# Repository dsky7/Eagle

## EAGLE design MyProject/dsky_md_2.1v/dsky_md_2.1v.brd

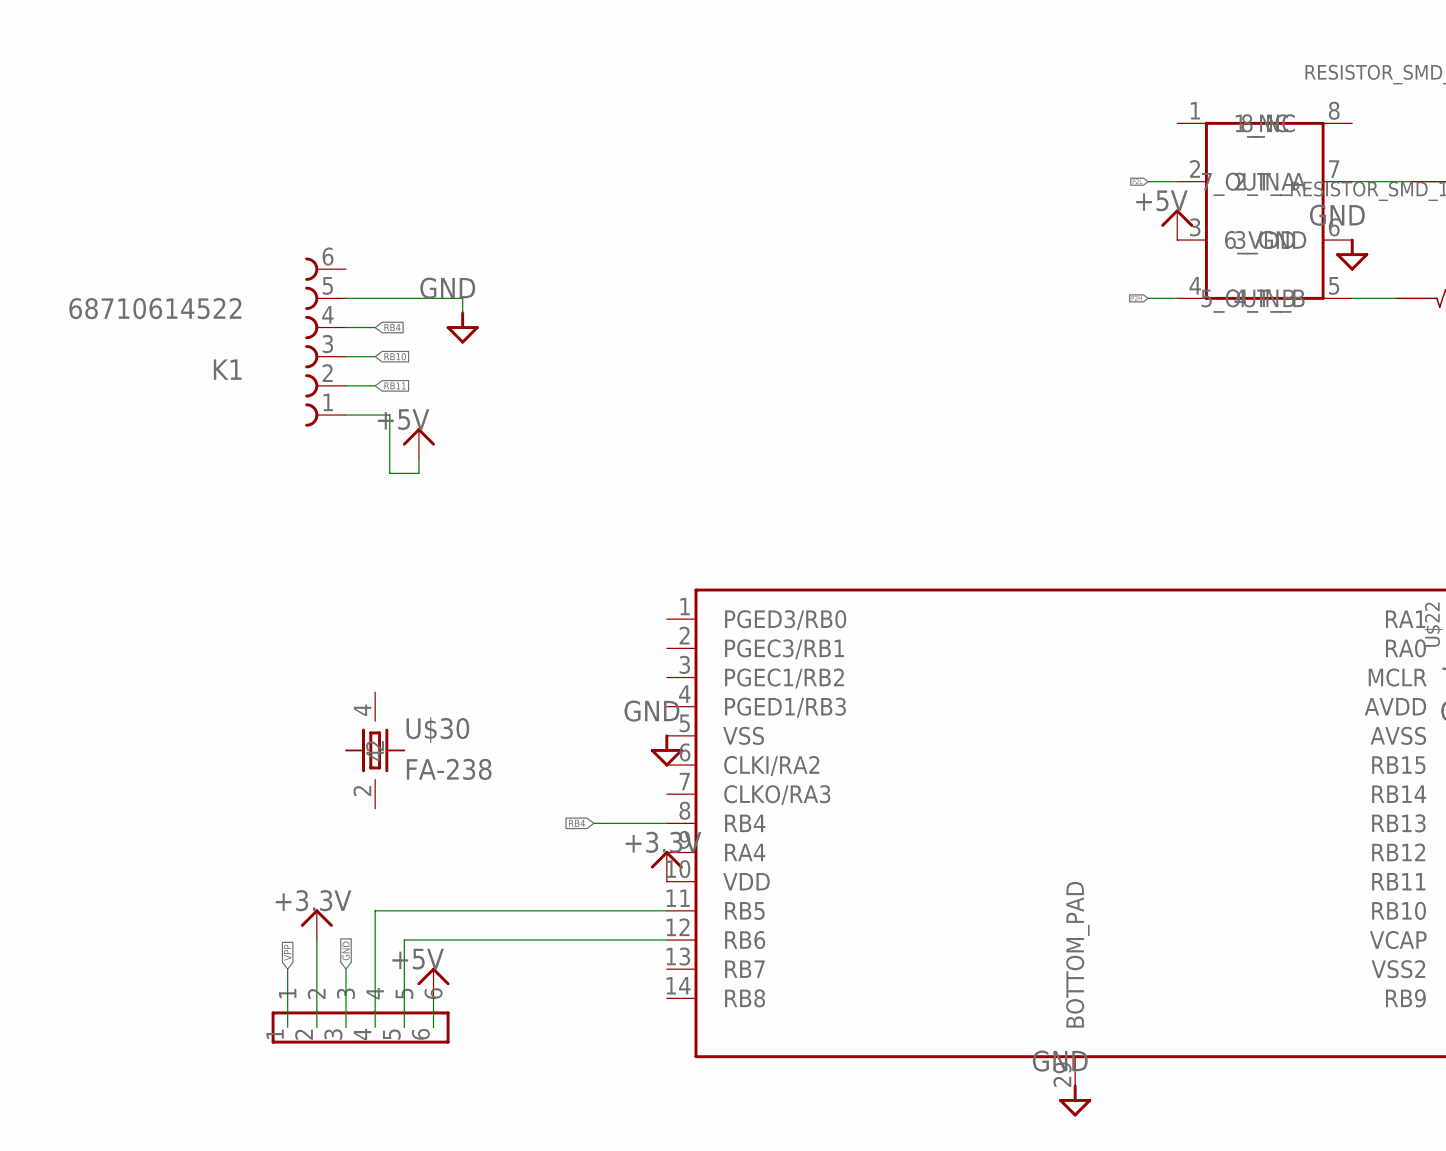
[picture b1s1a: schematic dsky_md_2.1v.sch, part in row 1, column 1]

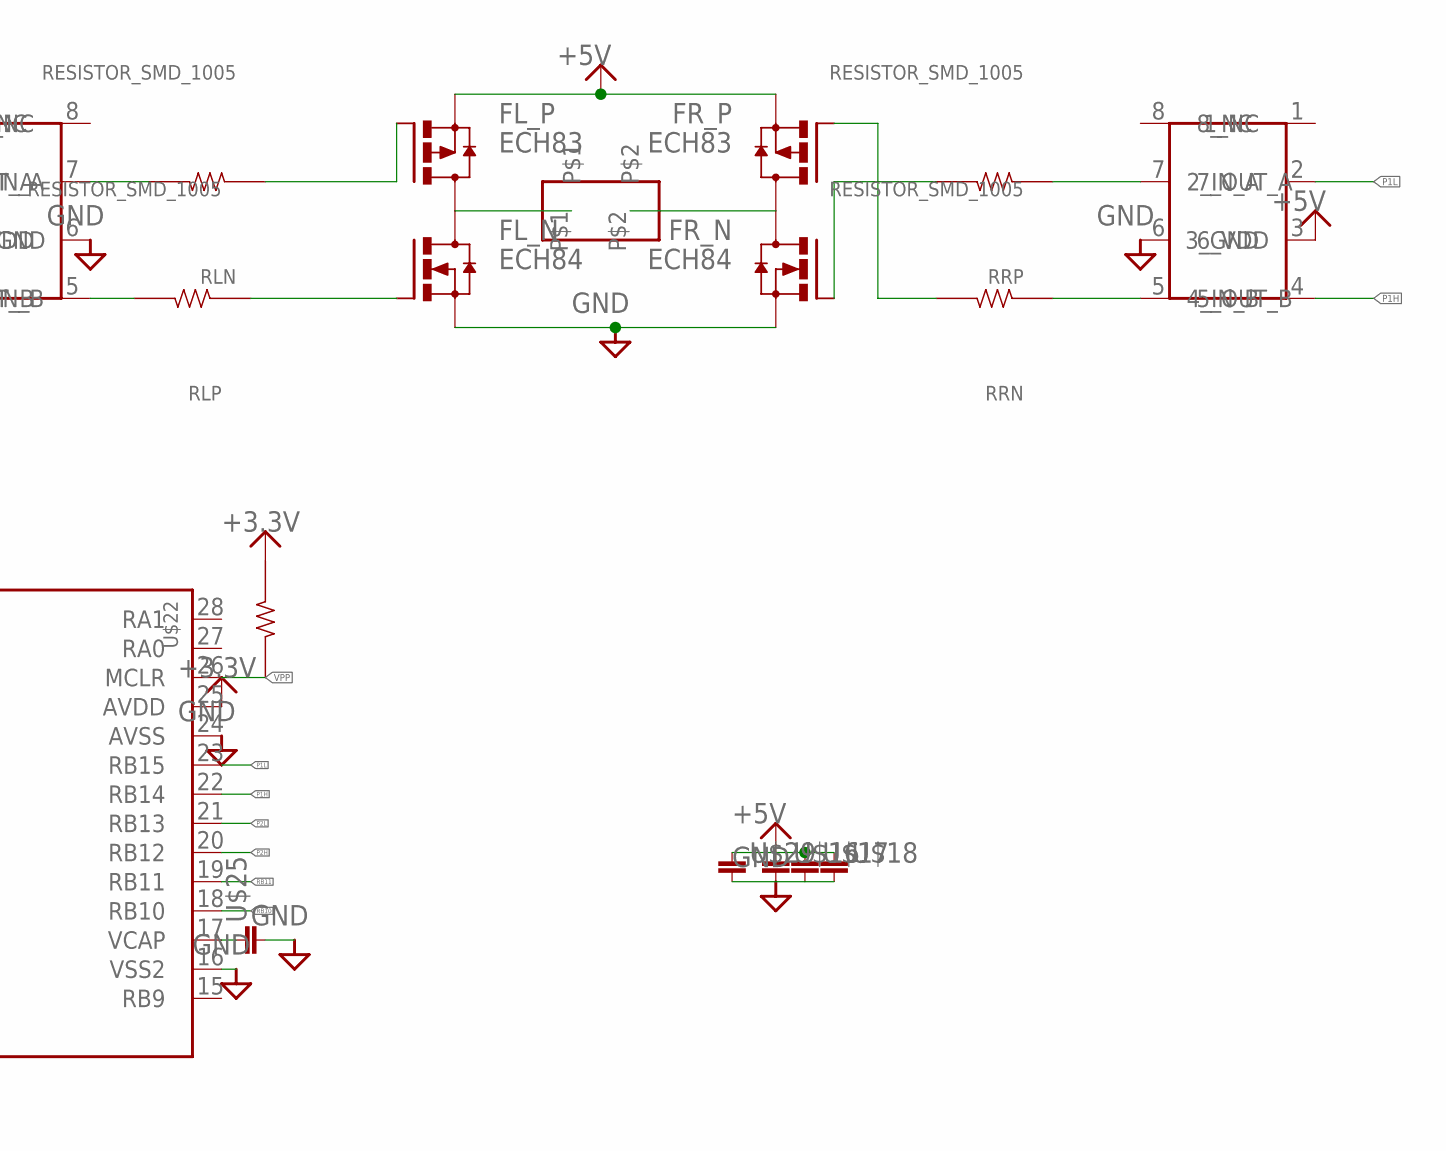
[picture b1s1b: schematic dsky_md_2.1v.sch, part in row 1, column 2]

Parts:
FL_N: ECH84; ECH8
FL_P: ECH83; ECH8
FR_N: ECH84; ECH8
FR_P: ECH83; ECH8
IC_L: TC1427COA; SOIC8
IC_R: TC1427COA; SOIC8
K1: 68710614522
RLN: RESISTOR_SMD_1005; 1005
RLP: RESISTOR_SMD_1005; 1005
RRN: RESISTOR_SMD_1005; 1005
RRP: RESISTOR_SMD_1005; 1005
U$3: PIN_HEADER_2; PIN_HEADER_2S
U$5: DSPIC33EP32MC202; QFN-S28_6X6MC
U$6: PIN_HEADER_HALF_6
U$16, U$17, U$18, U$25: 1608
U$22: RESISTOR__SMD; 1608
U$29: 2012
U$30: FA-238

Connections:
+3.3V: U$5.10 (VDD), U$5.25 (AVDD), U$6.2, U$22.2
+5V: FL_P.1 (S), FL_P.2 (S), FL_P.3 (S), FR_P.1 (S), FR_P.2 (S), FR_P.3 (S), IC_L.3 (3_GND), IC_R.3 (3_GND), K1.1, U$6.6, U$16.P$1 (1), U$17.P$1 (1), U$18.P$1 (1), U$29.1
GND: FL_N.1 (S), FL_N.2 (S), FL_N.3 (S), FR_N.1 (S), FR_N.2 (S), FR_N.3 (S), IC_L.6 (6_VDD), IC_R.6 (6_VDD), K1.5, U$5.5 (VSS), U$5.16 (VSS2), U$5.24 (AVSS), U$5.29 (BOTTOM_PAD), U$6.3, U$16.P$2 (2), U$17.P$2 (2), U$18.P$2 (2), U$25.P$2 (2), U$29.2
M_L: FL_N.5 (D), FL_N.6 (D), FL_N.7 (D), FL_N.8 (D), FL_P.5 (D), FL_P.6 (D), FL_P.7 (D), FL_P.8 (D), U$3.P$1
M_R: FR_N.5 (D), FR_N.6 (D), FR_N.7 (D), FR_N.8 (D), FR_P.5 (D), FR_P.6 (D), FR_P.7 (D), FR_P.8 (D), U$3.P$2
unnamed: FL_P.4 (G), RLN.1
unnamed: FL_N.4 (G), RLP.1
unnamed: IC_L.7 (7_OUT_A), RLN.2
unnamed: FR_P.4 (G), RRN.2
unnamed: IC_L.5 (5_OUT_B), RLP.2
unnamed: IC_R.7 (7_OUT_A), RRP.1
unnamed: U$5.17 (VCAP), U$25.P$1 (1)
unnamed: IC_R.5 (5_OUT_B), RRN.1
unnamed: U$5.11 (RB5), U$6.4
unnamed: U$5.12 (RB6), U$6.5
unnamed: FR_N.4 (G), RRP.2
P1H: IC_R.4 (4_IN_B), U$5.22 (RB14)
P1L: IC_R.2 (2_IN_A), U$5.23 (RB15)
P2H: IC_L.4 (4_IN_B), U$5.20 (RB12)
P2L: IC_L.2 (2_IN_A), U$5.21 (RB13)
RB4: K1.4, U$5.8 (RB4)
RB10: K1.3, U$5.18 (RB10)
RB11: K1.2, U$5.19 (RB11)
VPP: U$5.26 (MCLR), U$6.1, U$22.1

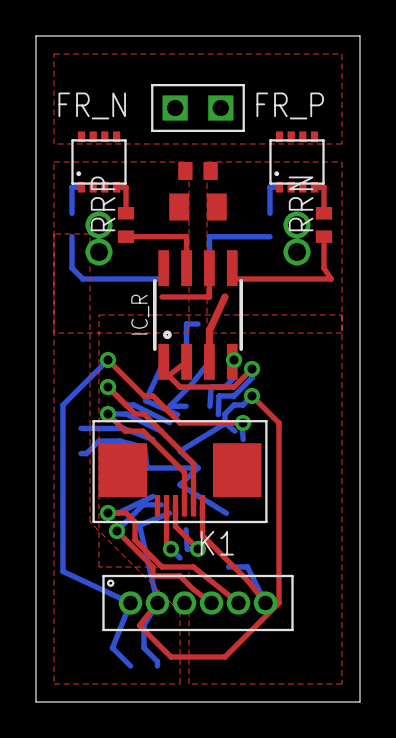
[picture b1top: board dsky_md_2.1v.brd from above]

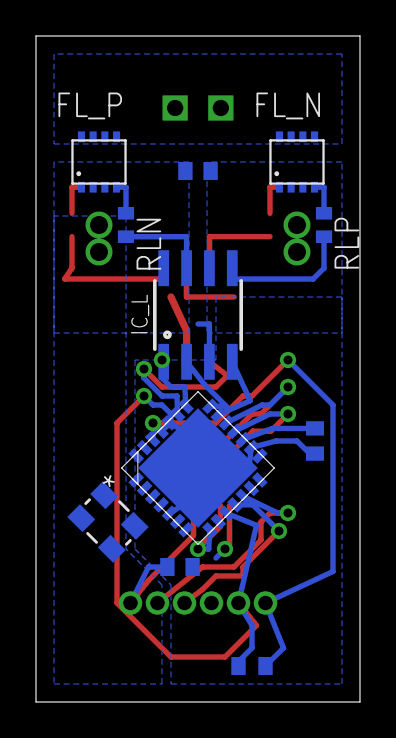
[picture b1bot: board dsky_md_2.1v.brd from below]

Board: 2 copper layers, 18.0 x 37.0 mm, 21 parts (11 on the bottom side), 24 nets.

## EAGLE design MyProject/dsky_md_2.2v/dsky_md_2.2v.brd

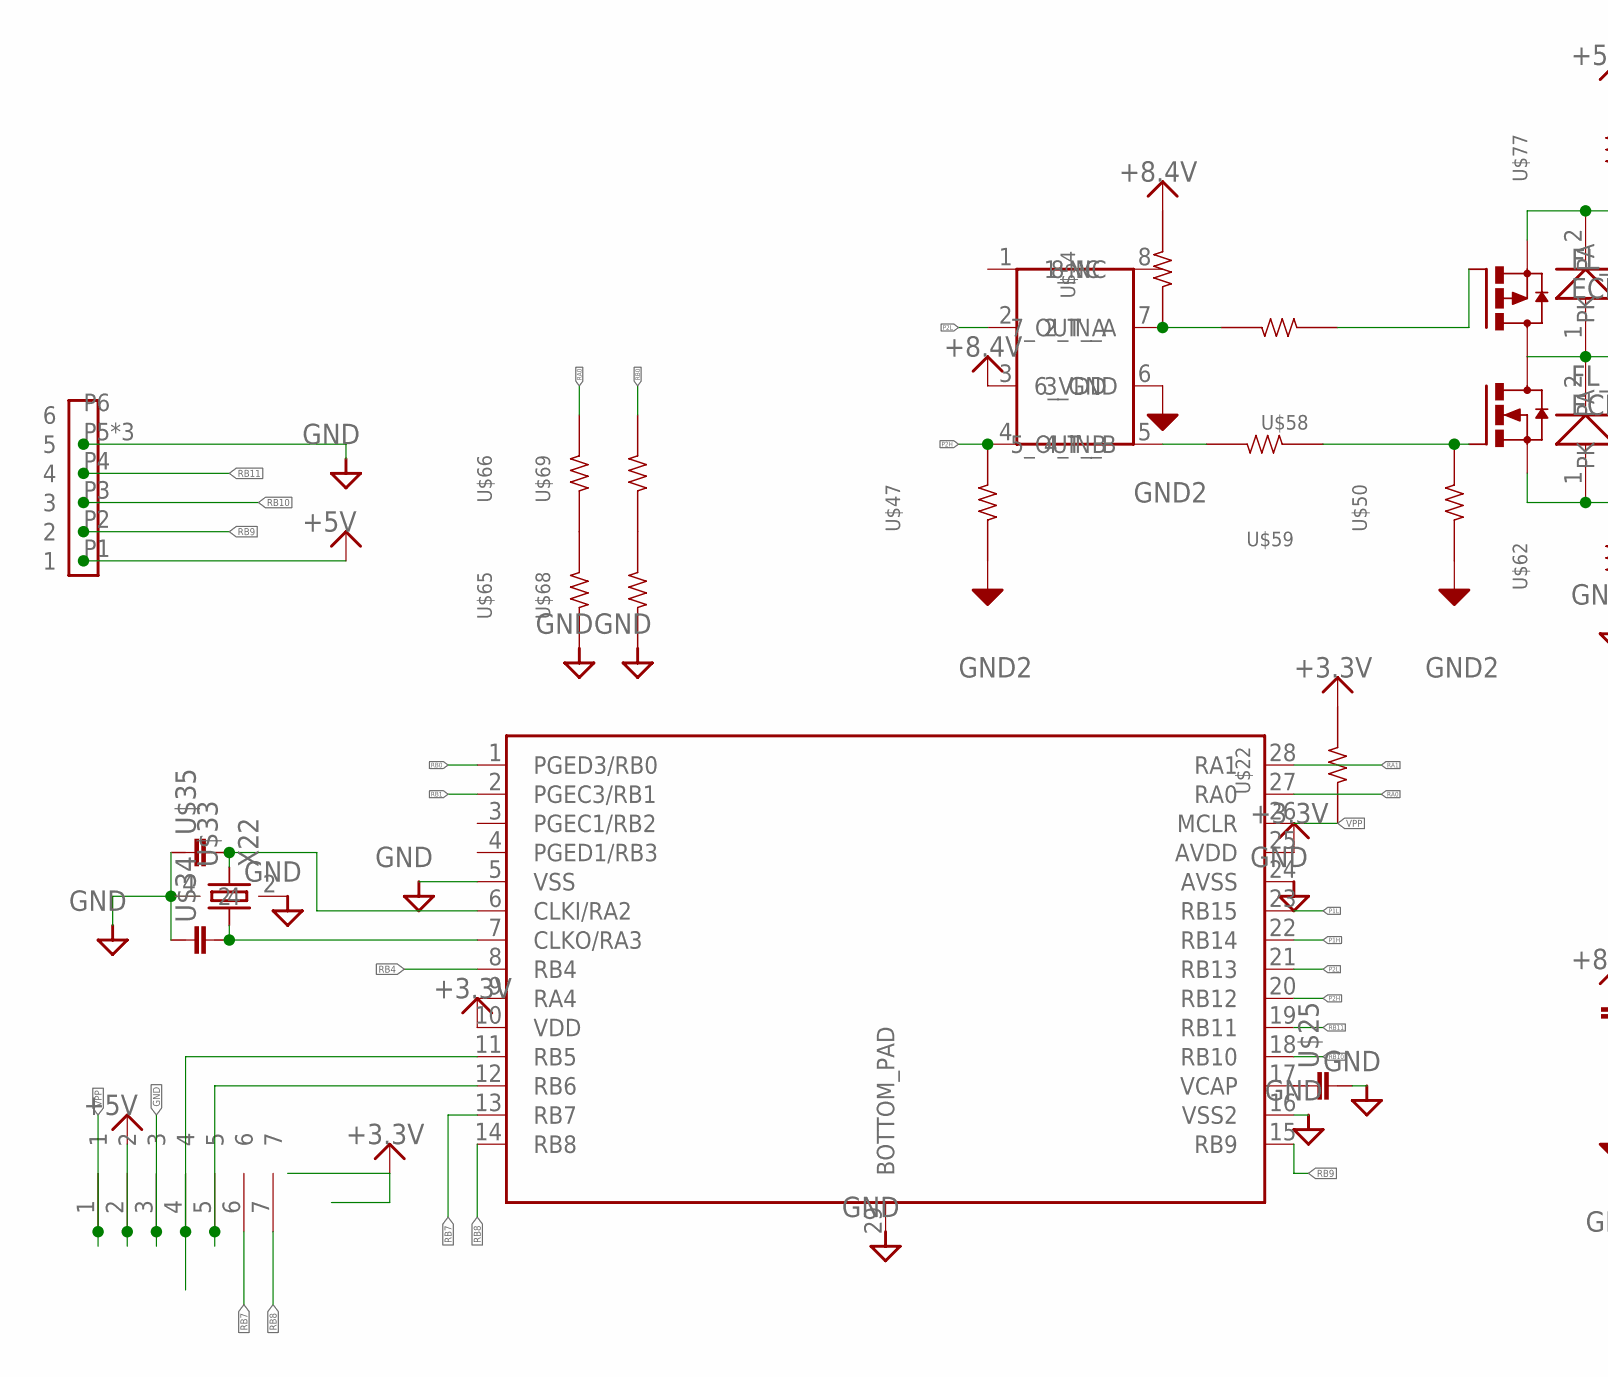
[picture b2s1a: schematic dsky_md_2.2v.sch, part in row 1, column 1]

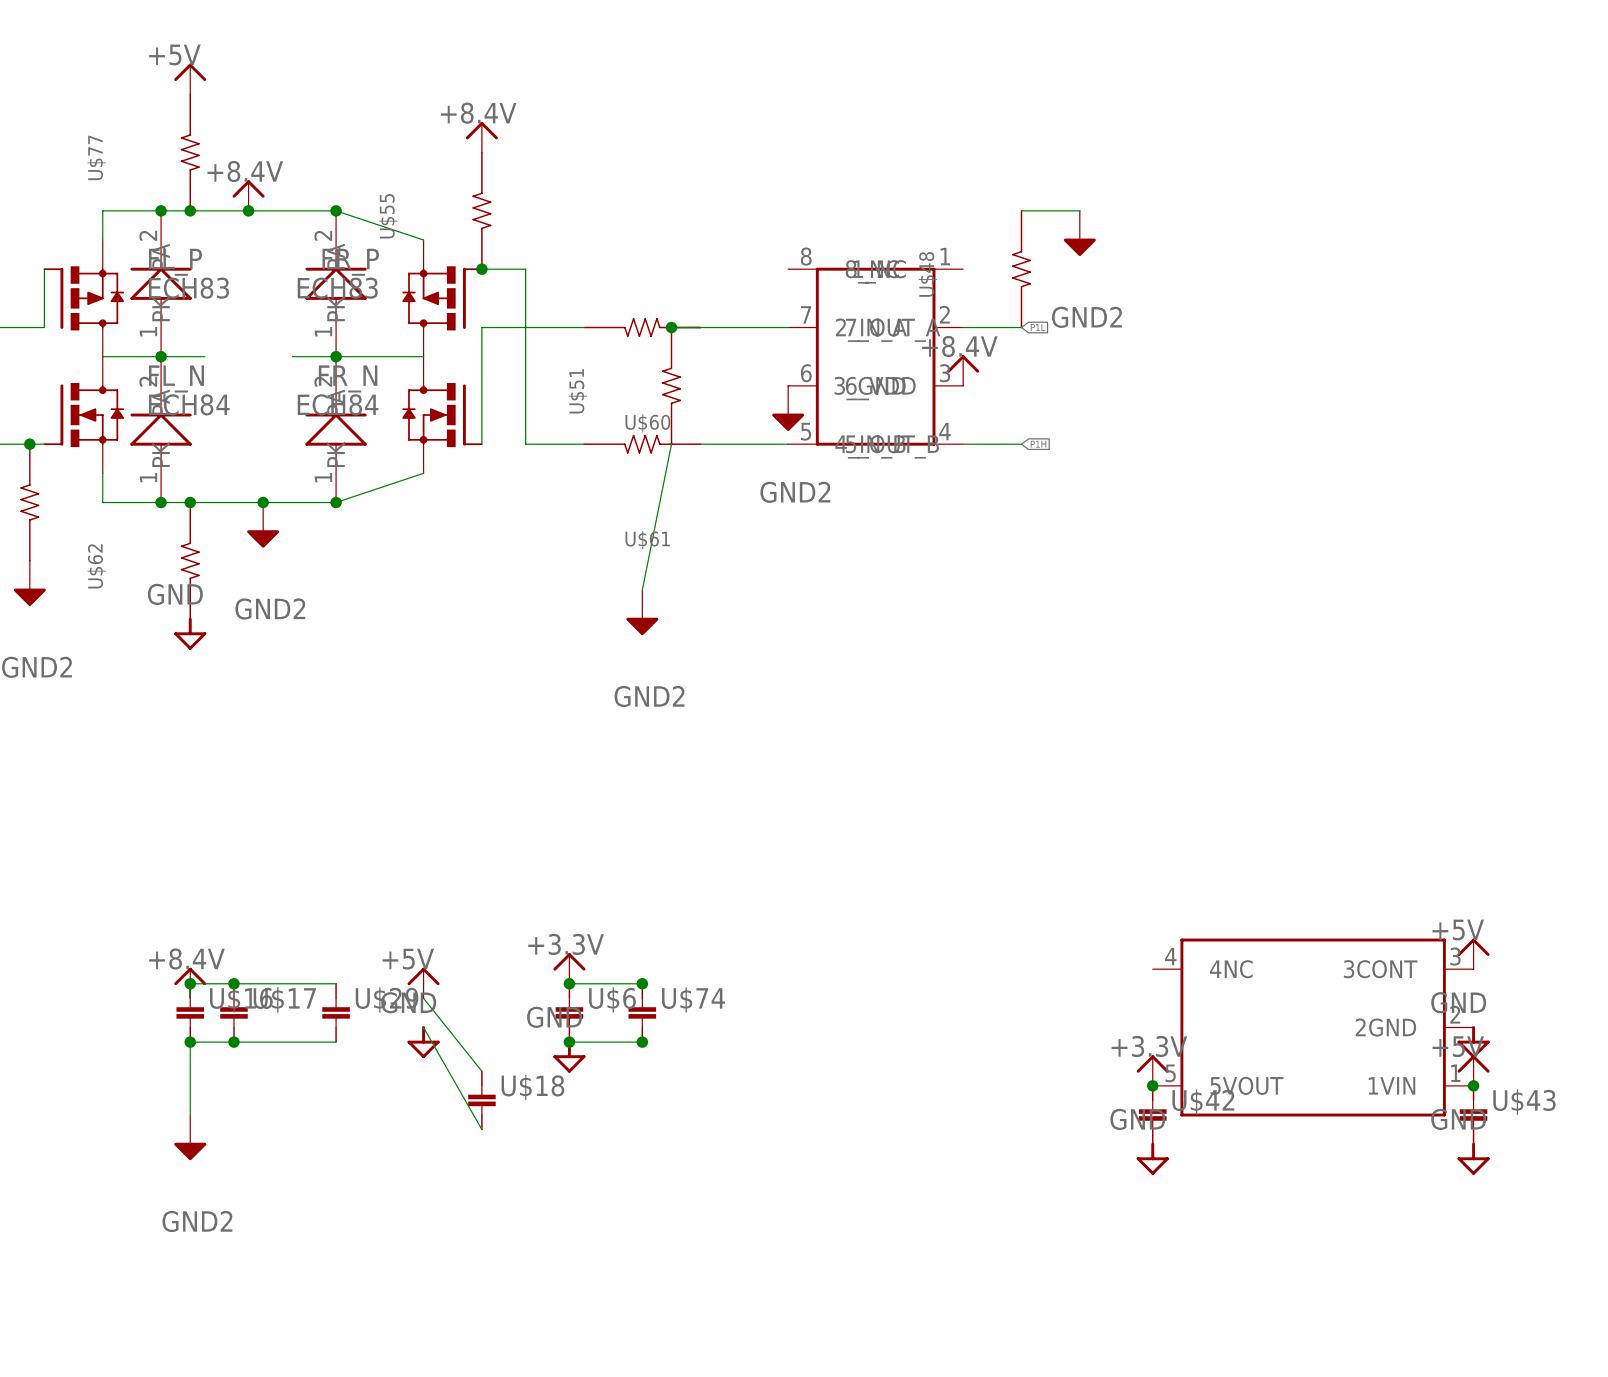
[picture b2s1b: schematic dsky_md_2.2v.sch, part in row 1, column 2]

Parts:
FL_N: ECH84; ECH8
FL_P: ECH83; ECH8
FR_N: ECH84; ECH8
FR_P: ECH83; ECH8
IC_L: TC1427COA; SOIC8
IC_R: TC1427COA; SOIC8
U$3: PIN_HEADER_7
U$5: DSPIC33EP32MC202; QFN-S28_6X6MC
U$6, U$16, U$17, U$18, U$25, U$34, U$35, U$42, U$43, U$74: 1608
U$22, U$47, U$48, U$50, U$51, U$54, U$55, U$58, U$59, U$60, U$61, U$62, U$65, U$66, U$68, U$69, U$77: RESISTOR__SMD; 1608
U$29: 2012
U$30: TAR5SB; SSOP5-P-0.95
U$33: X22; SMD_X22
U$44: FH12-6S-0.5; FPC6
U$70, U$71, U$72, U$73: SS2040; SOD-123FL

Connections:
+3.3V: U$5.10 (VDD), U$5.25 (AVDD), U$6.P$1 (1), U$22.2, U$30.5 (5VOUT), U$42.P$1 (1), U$74.P$1 (1)
+5V: U$3.2, U$18.P$1 (1), U$30.1 (1VIN), U$30.3 (3CONT), U$43.P$1 (1), U$44.P1 (1), U$77.2
+8.4V: FL_P.1 (S), FL_P.2 (S), FL_P.3 (S), FR_P.1 (S), FR_P.2 (S), FR_P.3 (S), IC_L.3 (3_GND), IC_R.3 (3_GND), U$16.P$1 (1), U$17.P$1 (1), U$29.1, U$54.2, U$55.2, U$70.2 (PK), U$73.2 (PK), U$77.1
GND: U$3.3, U$5.5 (VSS), U$5.16 (VSS2), U$5.24 (AVSS), U$5.29 (BOTTOM_PAD), U$6.P$2 (2), U$18.P$2 (2), U$25.P$2 (2), U$30.2 (2GND), U$33.2, U$33.4, U$34.P$1 (1), U$35.P$1 (1), U$42.P$2 (2), U$43.P$2 (2), U$44.P5 (5), U$44.P_NC1 (5), U$44.P_NC2 (5), U$62.1, U$65.1, U$68.1, U$74.P$2 (2)
GND2: FL_N.1 (S), FL_N.2 (S), FL_N.3 (S), FR_N.1 (S), FR_N.2 (S), FR_N.3 (S), IC_L.6 (6_VDD), IC_R.6 (6_VDD), U$16.P$2 (2), U$17.P$2 (2), U$29.2, U$47.1, U$48.2, U$50.1, U$51.1, U$62.2, U$71.1 (PA), U$72.1 (PA)
M_L: FL_N.5 (D), FL_N.6 (D), FL_N.7 (D), FL_N.8 (D), FL_P.5 (D), FL_P.6 (D), FL_P.7 (D), FL_P.8 (D), U$70.1 (PA), U$71.2 (PK)
M_R: FR_N.5 (D), FR_N.6 (D), FR_N.7 (D), FR_N.8 (D), FR_P.5 (D), FR_P.6 (D), FR_P.7 (D), FR_P.8 (D), U$72.2 (PK), U$73.1 (PA)
unnamed: FL_P.4 (G), U$58.1
unnamed: FL_N.4 (G), U$50.2, U$59.1
unnamed: IC_L.7 (7_OUT_A), U$54.1, U$58.2
unnamed: FR_P.4 (G), U$55.1, U$61.2
unnamed: IC_L.5 (5_OUT_B), U$59.2
unnamed: IC_R.7 (7_OUT_A), U$51.2, U$60.1
unnamed: U$5.17 (VCAP), U$25.P$1 (1)
unnamed: U$5.7 (CLKO/RA3), U$33.1, U$34.P$2 (2)
unnamed: IC_R.5 (5_OUT_B), U$61.1
unnamed: U$3.4, U$5.11 (RB5)
unnamed: U$3.5, U$5.12 (RB6)
unnamed: FR_N.4 (G), U$60.2
unnamed: U$5.6 (CLKI/RA2), U$33.3, U$35.P$2 (2)
unnamed: U$65.2, U$66.1
unnamed: U$68.2, U$69.1
P1H: IC_R.4 (4_IN_B), U$5.22 (RB14)
P1L: IC_R.2 (2_IN_A), U$5.23 (RB15), U$48.1
P2H: IC_L.4 (4_IN_B), U$5.20 (RB12), U$47.2
P2L: IC_L.2 (2_IN_A), U$5.21 (RB13)
RA0: U$5.27 (RA0), U$66.2
RA1: U$5.28 (RA1)
RB0: U$5.1 (PGED3/RB0), U$69.2
RB1: U$5.2 (PGEC3/RB1)
RB4: U$5.8 (RB4)
RB7: U$3.6, U$5.13 (RB7)
RB8: U$3.7, U$5.14 (RB8)
RB9: U$5.15 (RB9), U$44.P2 (2)
RB10: U$5.18 (RB10), U$44.P3 (3)
RB11: U$5.19 (RB11), U$44.P4 (4)
VPP: U$3.1, U$5.26 (MCLR), U$22.1

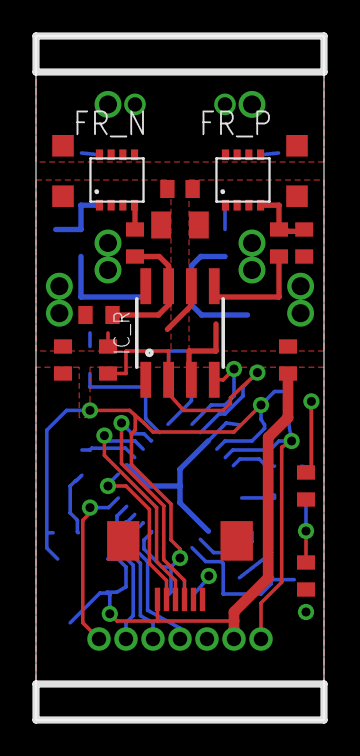
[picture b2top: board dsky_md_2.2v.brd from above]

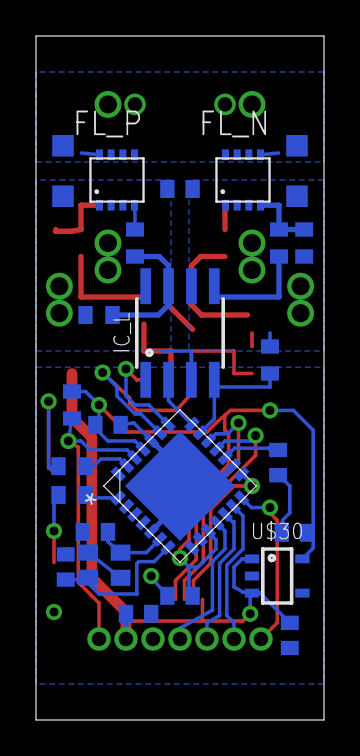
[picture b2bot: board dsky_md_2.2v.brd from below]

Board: 2 copper layers, 16.0 x 38.0 mm, 43 parts (25 on the bottom side), 34 nets.

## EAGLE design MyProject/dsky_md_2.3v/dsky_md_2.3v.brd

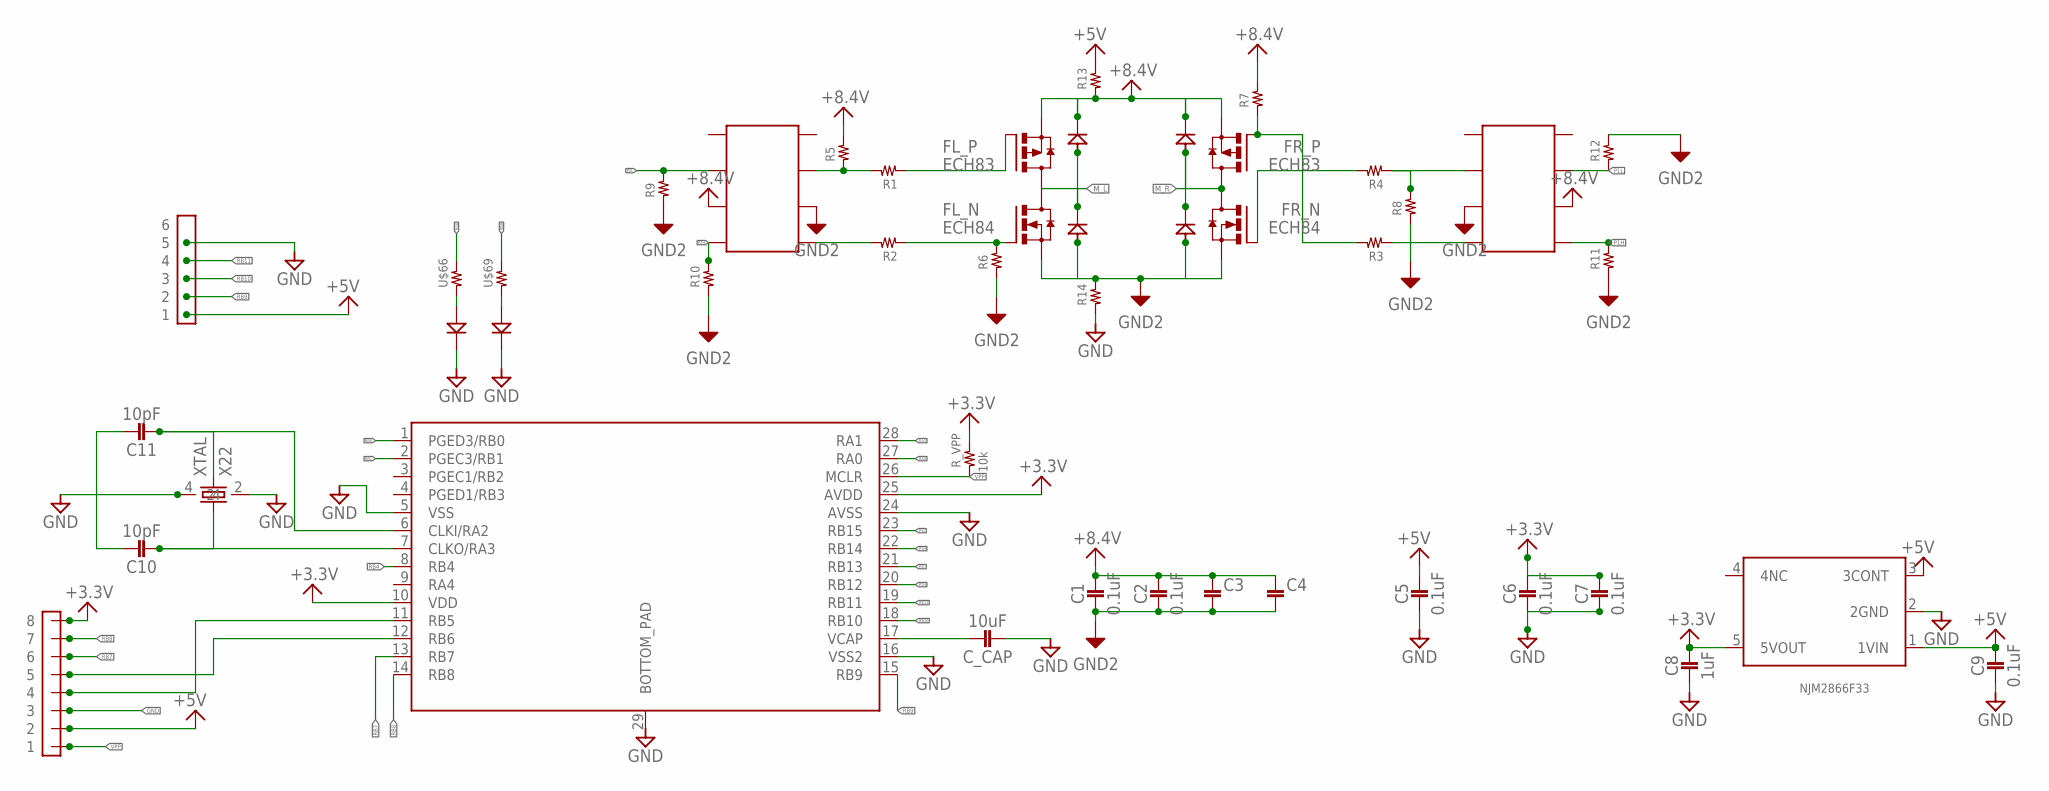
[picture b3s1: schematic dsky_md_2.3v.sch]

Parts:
C1, C2, C5, C6, C7, C9: 0.1uF; 1608
C3, C4: 2012
C8: 1uF; 1608
C10, C11: 10pF; 1608
C_CAP: 10uF; 1608
FL_N: ECH84; ECH8
FL_P: ECH83; ECH8
FR_N: ECH84; ECH8
FR_P: ECH83; ECH8
IC_L: TC1427COA; SOIC8
IC_R: TC1427COA; SOIC8
NJM2866F33: TAR5SB; SSOP5-P-0.95
R1, R2, R3, R4, R5, R6, R7, R8, R9, R10, R11, R12, R13, R14: RESISTOR__SMD; 1608
R_VPP: 10k; 1608
U$3, U$70, U$71, U$73: SS2040; SOD-123FL
U$5: DSPIC33EP32MC202; QFN-S28_6X6MC
U$6, U$16: 1608
U$44: FH12-6S-0.5; FPC6
U$66, U$69: RESISTOR__SMD; 1608
U$80: PIN_HEADER_8
XTAL: X22; SMD_X22

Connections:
+3.3V: C6.P$1 (1), C7.P$1 (1), C8.P$1 (1), NJM2866F33.5 (5VOUT), R_VPP.2, U$5.10 (VDD), U$5.25 (AVDD), U$80.8
+5V: C5.P$1 (1), C9.P$1 (1), NJM2866F33.1 (1VIN), NJM2866F33.3 (3CONT), R13.2, U$44.P1 (1), U$80.2
+8.4V: C1.P$1 (1), C2.P$1 (1), C3.1, C4.1, FL_P.1 (S), FL_P.2 (S), FL_P.3 (S), FR_P.1 (S), FR_P.2 (S), FR_P.3 (S), IC_L.3 (3_GND), IC_R.3 (3_GND), R5.2, R7.2, R13.1, U$70.2 (PK), U$73.2 (PK)
GND: C5.P$2 (2), C6.P$2 (2), C7.P$2 (2), C8.P$2 (2), C9.P$2 (2), C10.P$1 (1), C11.P$1 (1), C_CAP.P$2 (2), NJM2866F33.2 (2GND), R14.1, U$5.5 (VSS), U$5.16 (VSS2), U$5.24 (AVSS), U$5.29 (BOTTOM_PAD), U$6.2 (K), U$16.2 (K), U$44.P5 (5), U$44.P_NC1 (5), U$44.P_NC2 (5), U$80.3, XTAL.2, XTAL.4
GND2: C1.P$2 (2), C2.P$2 (2), C3.2, C4.2, FL_N.1 (S), FL_N.2 (S), FL_N.3 (S), FR_N.1 (S), FR_N.2 (S), FR_N.3 (S), IC_L.6 (6_VDD), IC_R.6 (6_VDD), R6.1, R8.1, R9.1, R10.1, R11.1, R12.2, R14.2, U$3.1 (PA), U$71.1 (PA)
M_L: FL_N.5 (D), FL_N.6 (D), FL_N.7 (D), FL_N.8 (D), FL_P.5 (D), FL_P.6 (D), FL_P.7 (D), FL_P.8 (D), U$3.2 (PK), U$70.1 (PA)
M_R: FR_N.5 (D), FR_N.6 (D), FR_N.7 (D), FR_N.8 (D), FR_P.5 (D), FR_P.6 (D), FR_P.7 (D), FR_P.8 (D), U$71.2 (PK), U$73.1 (PA)
unnamed: FL_P.4 (G), R1.1
unnamed: FL_N.4 (G), R2.1, R6.2
unnamed: IC_L.7 (7_OUT_A), R1.2, R5.1
unnamed: FR_P.4 (G), R3.2, R7.1
unnamed: IC_L.5 (5_OUT_B), R2.2
unnamed: IC_R.7 (7_OUT_A), R4.1, R8.2
unnamed: C_CAP.P$1 (1), U$5.17 (VCAP)
unnamed: C10.P$2 (2), U$5.7 (CLKO/RA3), XTAL.1
unnamed: IC_R.5 (5_OUT_B), R3.1
unnamed: U$5.11 (RB5), U$80.4
unnamed: U$5.12 (RB6), U$80.5
unnamed: FR_N.4 (G), R4.2
unnamed: C11.P$2 (2), U$5.6 (CLKI/RA2), XTAL.3
unnamed: U$6.1 (A), U$66.1
unnamed: U$16.1 (A), U$69.1
P1H: IC_R.4 (4_IN_B), R11.2, U$5.22 (RB14)
P1L: IC_R.2 (2_IN_A), R12.1, U$5.23 (RB15)
P2H: IC_L.4 (4_IN_B), R10.2, U$5.20 (RB12)
P2L: IC_L.2 (2_IN_A), R9.2, U$5.21 (RB13)
RA0: U$5.27 (RA0), U$66.2
RA1: U$5.28 (RA1)
RB0: U$5.1 (PGED3/RB0), U$69.2
RB1: U$5.2 (PGEC3/RB1)
RB4: U$5.8 (RB4)
RB7: U$5.13 (RB7), U$80.6
RB8: U$5.14 (RB8), U$80.7
RB9: U$5.15 (RB9), U$44.P2 (2)
RB10: U$5.18 (RB10), U$44.P3 (3)
RB11: U$5.19 (RB11), U$44.P4 (4)
VPP: R_VPP.1, U$5.26 (MCLR), U$80.1

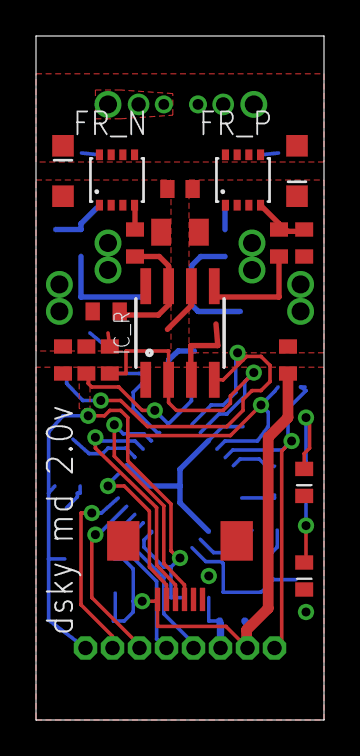
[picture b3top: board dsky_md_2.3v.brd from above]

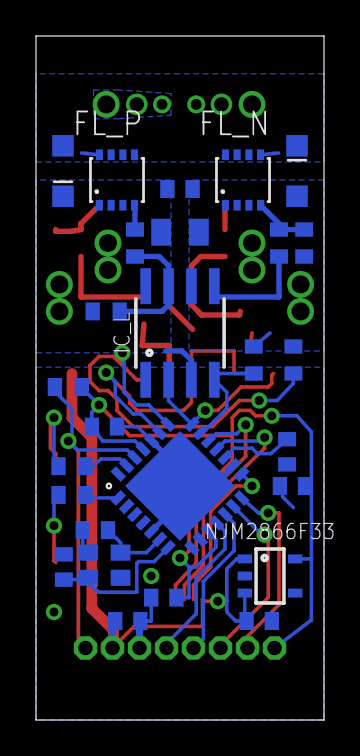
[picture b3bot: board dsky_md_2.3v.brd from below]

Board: 2 copper layers, 16.0 x 38.0 mm, 46 parts (27 on the bottom side), 34 nets.

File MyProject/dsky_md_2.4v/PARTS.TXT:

Partlist

Exported from dsky_md_2.4v.sch at 2013/10/17 20:07:16

EAGLE Version 6.5.0 Copyright (c) 1988-2013 CadSoft

Assembly variant: 

Part       Value            Device           Package       Library         Sheet

C1         0.1uF            1608             1608          02_C            1
C2         0.1uF            1608             1608          02_C            1
C3         4.7u             2012             2012          02_C            1
C4         4.7u             2012             2012          02_C            1
C5         0.1uF            1608             1608          02_C            1
C6         0.1uF            1608             1608          02_C            1
C7         0.1uF            1608             1608          02_C            1
C8         1uF              1608             1608          02_C            1
C9         0.1uF            1608             1608          02_C            1
C10        10pF             1608             1608          02_C            1
C11        10pF             1608             1608          02_C            1
CN1        FH12-6S-0.5      FH12-6S-0.5      FPC6          08_CONECTOR     1
C_CAP      10uF             1608             1608          02_C            1
D1         SS2040           SS2040           SOD-123FL     DIODE           1
D2         SS2040           SS2040           SOD-123FL     DIODE           1
D3         SS2040           SS2040           SOD-123FL     DIODE           1
D4         SS2040           SS2040           SOD-123FL     DIODE           1
FET1       ECH83            ECH83            ECH8          06_FET          1
FET2       ECH84            ECH84            ECH8          06_FET          1
FET3       ECH83            ECH83            ECH8          06_FET          1
FET4       ECH84            ECH84            ECH8          06_FET          1
IC1        DSPIC33EP32MC202 DSPIC33EP32MC202 QFN-S28_6X6MC microchip-dspic 1
IC2        NJM2866F33       TAR5SB           SSOP5-P-0.95  04_IC           1
IC3        TC1427COA        TC1427COA        SOIC8         04_IC           1
IC4        TC1427COA        TC1427COA        SOIC8         04_IC           1
LED1       1608             1608             1608          LED             1
LED2       1608             1608             1608          LED             1
PIN_HEADER PIN_HEADER_8     PIN_HEADER_8     PIN_HEADER_8  08_CONECTOR     1
R1         10               RESISTOR__SMD    1608          01_R            1
R2         10               RESISTOR__SMD    1608          01_R            1
R3         10               RESISTOR__SMD    1608          01_R            1
R4         10               RESISTOR__SMD    1608          01_R            1
R5         10K              RESISTOR__SMD    1608          01_R            1
R6         10K              RESISTOR__SMD    1608          01_R            1
R7         10K              RESISTOR__SMD    1608          01_R            1
R8         10K              RESISTOR__SMD    1608          01_R            1
R9         10K              RESISTOR__SMD    1608          01_R            1
R10        10K              RESISTOR__SMD    1608          01_R            1
R11        10K              RESISTOR__SMD    1608          01_R            1
R12        10K              RESISTOR__SMD    1608          01_R            1
R13        0                RESISTOR__SMD    1608          01_R            1
R14        0                RESISTOR__SMD    1608          01_R            1
R15        200?             RESISTOR__SMD    1608          01_R            1
R16        470?             RESISTOR__SMD    1608          01_R            1
R_VPP      10k              RESISTOR__SMD    1608          01_R            1
XTAL       X22              X22              SMD_X22       09_2_CRYSTAL    1

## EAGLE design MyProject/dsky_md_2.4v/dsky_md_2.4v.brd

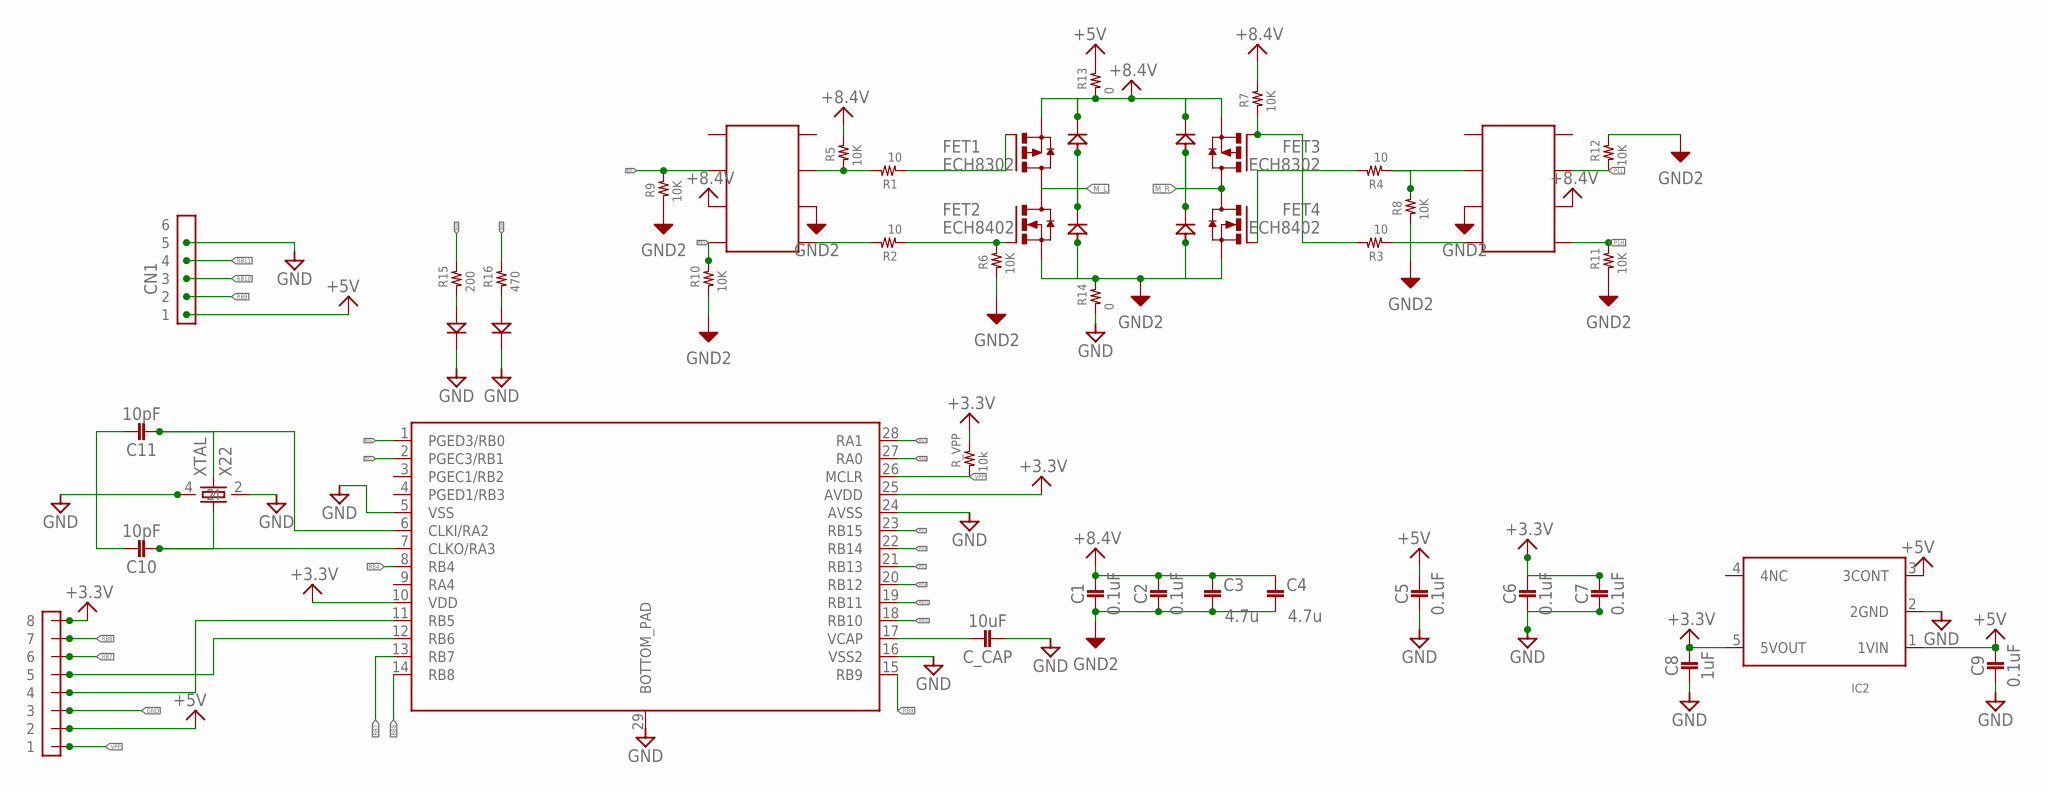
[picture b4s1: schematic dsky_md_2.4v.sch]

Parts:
C1, C2, C5, C6, C7, C9: 0.1uF; 1608
C3, C4: 4.7u; 2012
C8: 1uF; 1608
C10, C11: 10pF; 1608
CN1: FH12-6S-0.5; FPC6
C_CAP: 10uF; 1608
D1, D2, D3, D4: SS2040; SOD-123FL
FET1, FET3: ECH8302; ECH8
FET2, FET4: ECH8402; ECH8
IC1: DSPIC33EP32MC202; QFN-S28_6X6MC
IC2: NJM2866F33; SSOP5-P-0.95
IC3, IC4: TC1427COA; SOIC8
LED1, LED2: 1608
PIN_HEADER: PIN_HEADER_8
R1, R2, R3, R4: 10; 1608
R5, R6, R7, R8, R9, R10, R11, R12: 10K; 1608
R13, R14: 0; 1608
R15: 200; 1608
R16: 470; 1608
R_VPP: 10k; 1608
XTAL: X22; SMD_X22

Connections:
+3.3V: C6.P$1 (1), C7.P$1 (1), C8.P$1 (1), IC1.10 (VDD), IC1.25 (AVDD), IC2.5 (5VOUT), PIN_HEADER.8, R_VPP.2
+5V: C5.P$1 (1), C9.P$1 (1), CN1.P1 (1), IC2.1 (1VIN), IC2.3 (3CONT), PIN_HEADER.2, R13.2
+8.4V: C1.P$1 (1), C2.P$1 (1), C3.1, C4.1, D1.2 (PK), D3.2 (PK), FET1.1 (S), FET1.2 (S), FET1.3 (S), FET3.1 (S), FET3.2 (S), FET3.3 (S), IC3.3 (3_GND), IC4.3 (3_GND), R5.2, R7.2, R13.1
GND: C5.P$2 (2), C6.P$2 (2), C7.P$2 (2), C8.P$2 (2), C9.P$2 (2), C10.P$1 (1), C11.P$1 (1), CN1.P5 (5), CN1.P_NC1 (5), CN1.P_NC2 (5), C_CAP.P$2 (2), IC1.5 (VSS), IC1.16 (VSS2), IC1.24 (AVSS), IC1.29 (BOTTOM_PAD), IC2.2 (2GND), LED1.2 (K), LED2.2 (K), PIN_HEADER.3, R14.1, XTAL.2, XTAL.4
GND2: C1.P$2 (2), C2.P$2 (2), C3.2, C4.2, D2.1 (PA), D4.1 (PA), FET2.1 (S), FET2.2 (S), FET2.3 (S), FET4.1 (S), FET4.2 (S), FET4.3 (S), IC3.6 (6_VDD), IC4.6 (6_VDD), R6.1, R8.1, R9.1, R10.1, R11.1, R12.2, R14.2
M_L: D1.1 (PA), D2.2 (PK), FET1.5 (D), FET1.6 (D), FET1.7 (D), FET1.8 (D), FET2.5 (D), FET2.6 (D), FET2.7 (D), FET2.8 (D)
M_R: D3.1 (PA), D4.2 (PK), FET3.5 (D), FET3.6 (D), FET3.7 (D), FET3.8 (D), FET4.5 (D), FET4.6 (D), FET4.7 (D), FET4.8 (D)
unnamed: FET1.4 (G), R1.1
unnamed: FET2.4 (G), R2.1, R6.2
unnamed: IC3.7 (7_OUT_A), R1.2, R5.1
unnamed: FET3.4 (G), R3.2, R7.1
unnamed: IC3.5 (5_OUT_B), R2.2
unnamed: IC4.7 (7_OUT_A), R4.1, R8.2
unnamed: C_CAP.P$1 (1), IC1.17 (VCAP)
unnamed: C10.P$2 (2), IC1.7 (CLKO/RA3), XTAL.1
unnamed: IC4.5 (5_OUT_B), R3.1
unnamed: IC1.11 (RB5), PIN_HEADER.4
unnamed: IC1.12 (RB6), PIN_HEADER.5
unnamed: FET4.4 (G), R4.2
unnamed: C11.P$2 (2), IC1.6 (CLKI/RA2), XTAL.3
unnamed: LED1.1 (A), R15.1
unnamed: LED2.1 (A), R16.1
P1H: IC1.22 (RB14), IC4.4 (4_IN_B), R11.2
P1L: IC1.23 (RB15), IC4.2 (2_IN_A), R12.1
P2H: IC1.20 (RB12), IC3.4 (4_IN_B), R10.2
P2L: IC1.21 (RB13), IC3.2 (2_IN_A), R9.2
RA0: IC1.27 (RA0), R15.2
RA1: IC1.28 (RA1)
RB0: IC1.1 (PGED3/RB0), R16.2
RB1: IC1.2 (PGEC3/RB1)
RB4: IC1.8 (RB4)
RB7: IC1.13 (RB7), PIN_HEADER.6
RB8: IC1.14 (RB8), PIN_HEADER.7
RB9: CN1.P2 (2), IC1.15 (RB9)
RB10: CN1.P3 (3), IC1.18 (RB10)
RB11: CN1.P4 (4), IC1.19 (RB11)
VPP: IC1.26 (MCLR), PIN_HEADER.1, R_VPP.1

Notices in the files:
parts and their libraries:
Wuerth_Elektronik_eiCan_03_ZIF_Connector: Copyright: Würth Elektronik
